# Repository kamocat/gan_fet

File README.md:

# gan_fet
Test boards for gallium-nitride mosfets

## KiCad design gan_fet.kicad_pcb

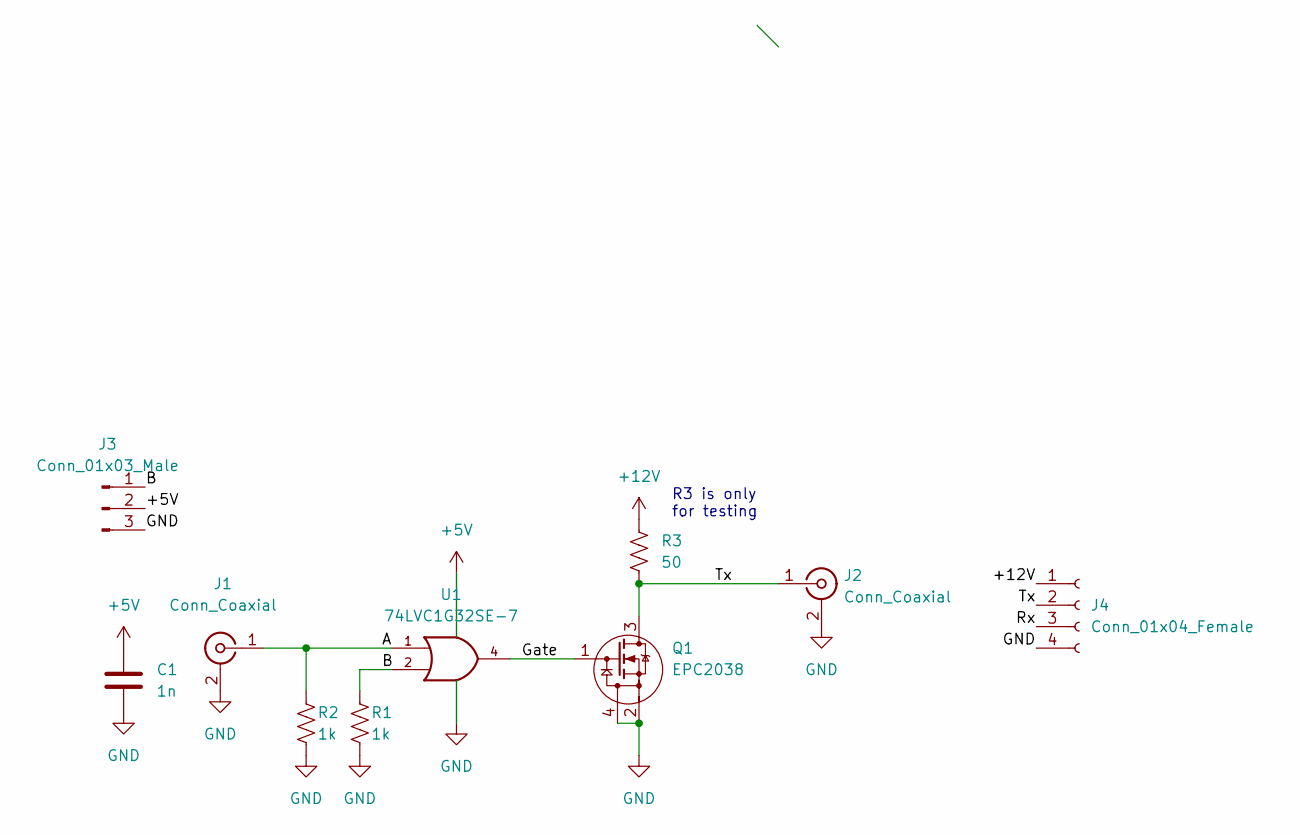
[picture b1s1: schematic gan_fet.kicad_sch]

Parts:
C1: 1n; C_0603_1608Metric
J1, J2: Conn_Coaxial; SMA_Amphenol_132289_EdgeMount
J3: Conn_01x03_Male; PinHeader_1x03_P2.54mm_Vertical
J4: Conn_01x04_Female; PinSocket_1x04_P2.54mm_Vertical
Q1: EPC2038; epc2036
R1, R2: 1k; R_0603_1608Metric
R3: 50; R_0603_1608Metric
U1: 74LVC1G32SE-7; SOT-353_SC-70-5

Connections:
+5V: C1.1, J3.2, U1.5 (VCC)
+12V: J4.1, R3.1
/A: J1.1 (In), R2.1, U1.1
/B: J3.1, R1.1, U1.2
/Gate: Q1.1 (G), U1.4
/Rx: J4.3
/Tx: J2.1 (In), J4.2, Q1.3 (D), R3.2
GND: C1.2, J1.2 (Ext), J2.2 (Ext), J3.3, J4.4, Q1.2 (S), Q1.4 (S), R1.2, R2.2, U1.3 (GND)

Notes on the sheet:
R3 is only for testing

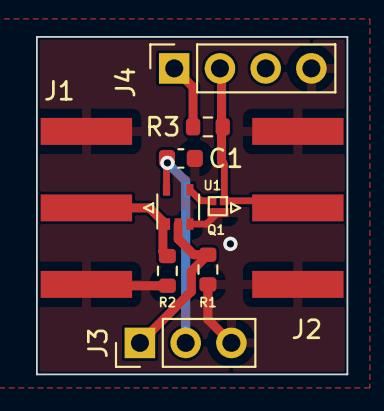
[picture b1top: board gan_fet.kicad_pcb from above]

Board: 2 copper layers, 17.2 x 18.8 mm, 10 parts (0 on the bottom side), 7 nets.

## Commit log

2022-06-21 EPC2036 in TO-220 package
2022-06-21 Increased trace width for mosfet drain and source
2022-07-07 layout changes
    rotate fet 45 degrees
    fills/vias for GND and Drain
2022-07-07 changed pinout, updated EPC footprint
2022-07-07 FET to backside, added PTH for BS170 pinout now matches IRF510 better EPC2036 footprint (pad and mask)
2022-07-07 Rev0 board to JLCPCB
2022-07-12 Added 3d model for mosfet
2022-07-13 Thermal simulation
2022-07-13 Ignored FreeCAD backup
2022-07-13 Need conformal mesh
2022-07-13 Made conformal mesh
2022-07-13 Removed unneeded parts to simplify meshing
    Also upgraded to FreeCAD 0.21 due to a bug in elmer/sifio.py
    Simple thermal simulation works, need to try multi-material
2022-07-14 Added copper to simulation, weird results
    Says the entire PCB is at aboslute zero
2022-07-14 Fixed PCB stackup dimensions
    Used parameters for OSH Park 2oz 0.8mm service
    https://docs.oshpark.com/services/two-layer-hhdc/
2022-07-14 Imported the traces using fcad_pcb macro instead of kSU
    Moved PCB schematic to the origin to make part placement easier
    Applied fixed temperatures for simulation rather than fixed power
2022-08-05 better stepfile and 3d symbol
2022-08-05 Fixed mosfet symbol and pinout
2022-08-18 Downsized board and replaced driver
2022-08-18 Downsized to reduce gate inductance
2022-08-18 Added header for standard filter board
    Moved R3 to tie to 12V instead of 5V
    Swapped inputs on OR gate
